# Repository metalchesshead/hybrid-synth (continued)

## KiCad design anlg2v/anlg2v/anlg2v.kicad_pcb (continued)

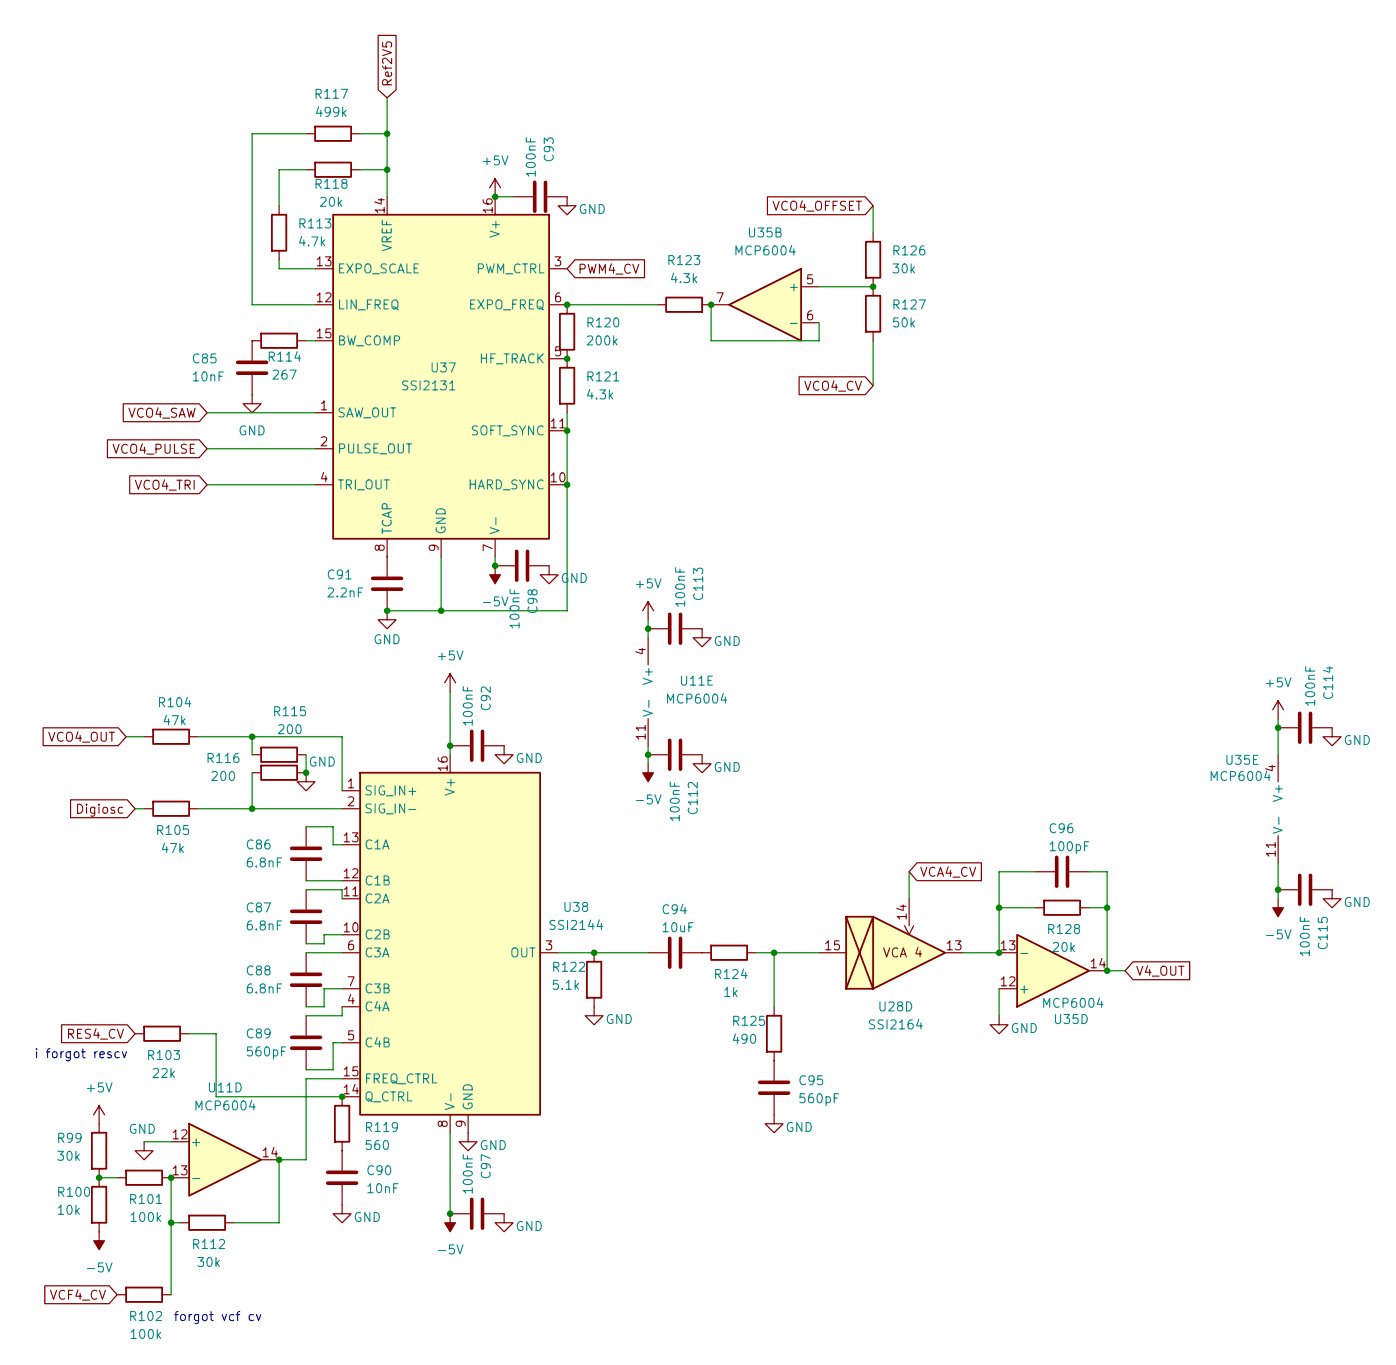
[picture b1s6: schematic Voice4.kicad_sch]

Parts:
C85, C90: 10nF; C_0402_1005Metric_Pad0.74x0.62mm_HandSolder
C86, C87, C88: 6.8nF; C_0402_1005Metric_Pad0.74x0.62mm_HandSolder
C89, C95: 560pF; C_0402_1005Metric_Pad0.74x0.62mm_HandSolder
C91: 2.2nF; C_0402_1005Metric_Pad0.74x0.62mm_HandSolder
C92, C93, C97, C98, C112, C113, C114, C115: 100nF; C_0402_1005Metric_Pad0.74x0.62mm_HandSolder
C94: 10uF; C_0402_1005Metric_Pad0.74x0.62mm_HandSolder
C96: 100pF; C_0402_1005Metric_Pad0.74x0.62mm_HandSolder
R99, R112, R126: 30k; R_0402_1005Metric
R100: 10k; R_0402_1005Metric
R101, R102: 100k; R_0402_1005Metric
R103: 22k; R_0402_1005Metric
R104, R105: 47k; R_0402_1005Metric
R113: 4.7k; R_0402_1005Metric
R114: 267; R_0402_1005Metric
R115, R116: 200; R_0402_1005Metric
R117: 499k; R_0402_1005Metric
R118, R128: 20k; R_0402_1005Metric
R119: 560; R_0402_1005Metric
R120: 200k; R_0402_1005Metric
R121, R123: 4.3k; R_0402_1005Metric
R122: 5.1k; R_0402_1005Metric
R124: 1k; R_0402_1005Metric
R125: 490; R_0402_1005Metric
R127: 50k; R_0402_1005Metric
U11, U35: MCP6004; SOIC-14_3.9x8.7mm_P1.27mm
U28: SSI2164; SOP-16_3.9x9.9mm_P1.27mm
U37: SSI2131; STC_SOP-16_3.9x9.9mm_P1.27mm
U38: SSI2144; SSOP-16_3.9x4.9mm_P0.635mm

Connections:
+5V: C92.2, C93.2, C113.2, C114.2, R99.1, U11.4 (V+), U35.4 (V+), U37.16 (V+), U38.16 (V+); also elsewhere on the board
-5V: C97.2, C98.2, C112.2, C115.2, R100.2, U11.11 (V-), U35.11 (V-), U37.7 (V-), U38.8 (V-); also elsewhere on the board
GND: C85.2, C90.2, C91.2, C92.1, C93.1, C95.2, C97.1, C98.1, C112.1, C113.1, C114.1, C115.1, R115.1, R116.1, R121.2, R122.2, U11.12 (+), U35.12 (+), U37.9 (GND), U37.10 (HARD_SYNC), U37.11 (SOFT_SYNC), U38.9 (GND); also elsewhere on the board
unnamed: C85.1, R114.2
unnamed: C90.1, R119.2
unnamed: C94.2, R124.2
unnamed: C95.1, R125.2
unnamed: R99.2, R100.1, R101.2
unnamed: R113.1, R118.2
unnamed: R124.1, R125.1, U28.15
unnamed: R101.1, R102.1, R112.2, U11.13 (-)
unnamed: R126.2, R127.1, U35.5 (+)
unnamed: R123.2, U35.6 (-), U35.7
unnamed: C96.1, R128.2, U28.13, U35.13 (-)
unnamed: R114.1, U37.15 (BW_COMP)
unnamed: R120.1, R123.1, U37.6 (EXPO_FREQ)
unnamed: R113.2, U37.13 (EXPO_SCALE)
unnamed: R120.2, R121.1, U37.5 (HF_TRACK)
unnamed: R117.2, U37.12 (LIN_FREQ)
unnamed: C91.1, U37.8 (TCAP)
unnamed: C86.1, U38.13 (C1A)
unnamed: C86.2, U38.12 (C1B)
unnamed: C87.1, U38.11 (C2A)
unnamed: C87.2, U38.10 (C2B)
unnamed: C88.1, U38.6 (C3A)
unnamed: C88.2, U38.7 (C3B)
unnamed: C89.1, U38.4 (C4A)
unnamed: C89.2, U38.5 (C4B)
unnamed: R112.1, U11.14, U38.15 (FREQ_CTRL)
unnamed: C94.1, R122.1, U38.3 (OUT)
unnamed: R103.1, R119.1, U38.14 (Q_CTRL)
unnamed: R104.1, R115.2, U38.1 (SIG_IN+)
unnamed: R105.1, R116.2, U38.2 (SIG_IN-)
PWM4_CV: U37.3 (PWM_CTRL); also elsewhere on the board
RES4_CV: R103.2; also elsewhere on the board
Ref2V5: R117.1, R118.1, U37.14 (VREF); also elsewhere on the board
V4_OUT: C96.2, R128.1, U35.14; also elsewhere on the board
VCA4_CV: U28.14; also elsewhere on the board
VCF4_CV: R102.2; also elsewhere on the board
VCO4_CV: R127.2; also elsewhere on the board
VCO4_OFFSET: R126.1; also elsewhere on the board
VCO4_OUT: R104.2; also elsewhere on the board
VCO4_PULSE: U37.2 (PULSE_OUT); also elsewhere on the board
VCO4_SAW: U37.1 (SAW_OUT); also elsewhere on the board
VCO4_TRI: U37.4 (TRI_OUT); also elsewhere on the board

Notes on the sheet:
forgot vcf cv
i forgot rescv

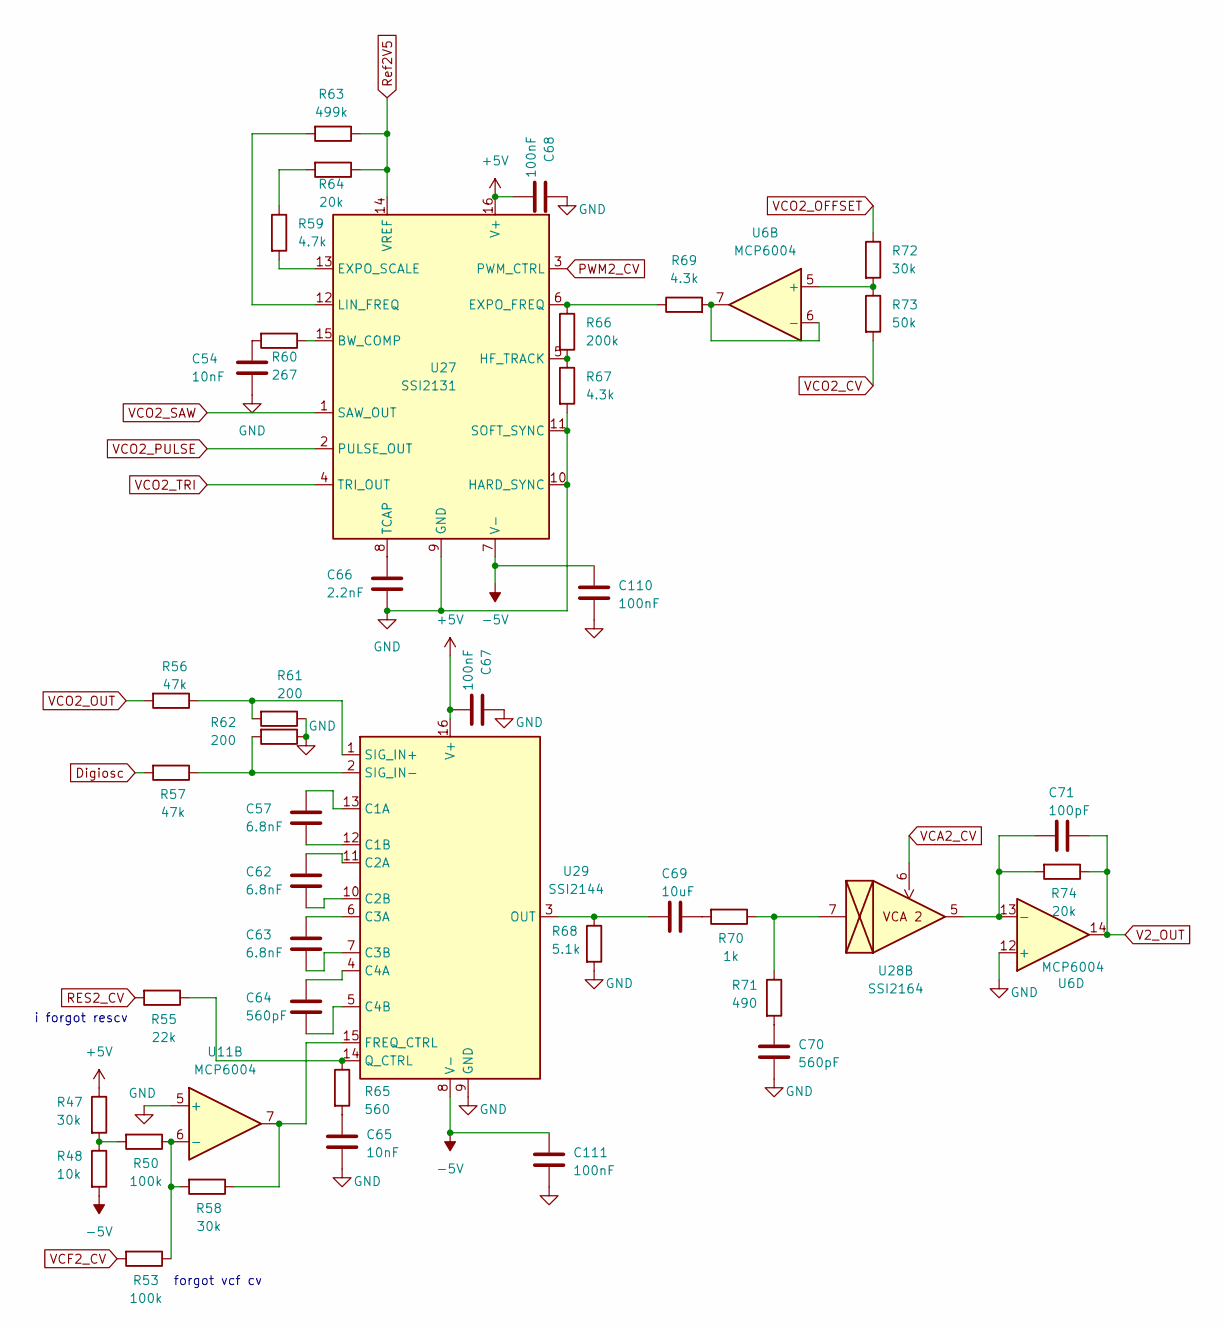
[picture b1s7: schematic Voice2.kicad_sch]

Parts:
C54, C65: 10nF; C_0402_1005Metric_Pad0.74x0.62mm_HandSolder
C57, C62, C63: 6.8nF; C_0402_1005Metric_Pad0.74x0.62mm_HandSolder
C64, C70: 560pF; C_0402_1005Metric_Pad0.74x0.62mm_HandSolder
C66: 2.2nF; C_0402_1005Metric_Pad0.74x0.62mm_HandSolder
C67, C68, C110, C111: 100nF; C_0402_1005Metric_Pad0.74x0.62mm_HandSolder
C69: 10uF; C_0402_1005Metric_Pad0.74x0.62mm_HandSolder
C71: 100pF; C_0402_1005Metric_Pad0.74x0.62mm_HandSolder
R47, R58, R72: 30k; R_0402_1005Metric
R48: 10k; R_0402_1005Metric
R50, R53: 100k; R_0402_1005Metric
R55: 22k; R_0402_1005Metric
R56, R57: 47k; R_0402_1005Metric
R59: 4.7k; R_0402_1005Metric
R60: 267; R_0402_1005Metric
R61, R62: 200; R_0402_1005Metric
R63: 499k; R_0402_1005Metric
R64, R74: 20k; R_0402_1005Metric
R65: 560; R_0402_1005Metric
R66: 200k; R_0402_1005Metric
R67, R69: 4.3k; R_0402_1005Metric
R68: 5.1k; R_0402_1005Metric
R70: 1k; R_0402_1005Metric
R71: 490; R_0402_1005Metric
R73: 50k; R_0402_1005Metric
U6, U11: MCP6004; SOIC-14_3.9x8.7mm_P1.27mm
U27: SSI2131; STC_SOP-16_3.9x9.9mm_P1.27mm
U28: SSI2164; SOP-16_3.9x9.9mm_P1.27mm
U29: SSI2144; SSOP-16_3.9x4.9mm_P0.635mm

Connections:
+5V: C67.2, C68.2, R47.1, U27.16 (V+), U29.16 (V+); also elsewhere on the board
-5V: C110.1, C111.1, R48.2, U27.7 (V-), U29.8 (V-); also elsewhere on the board
GND: C54.2, C65.2, C66.2, C67.1, C68.1, C70.2, C110.2, C111.2, R61.1, R62.1, R67.2, R68.2, U6.12 (+), U11.5 (+), U27.9 (GND), U27.10 (HARD_SYNC), U27.11 (SOFT_SYNC), U29.9 (GND); also elsewhere on the board
unnamed: C54.1, R60.2
unnamed: C65.1, R65.2
unnamed: C69.2, R70.2
unnamed: C70.1, R71.2
unnamed: R47.2, R48.1, R50.2
unnamed: R59.1, R64.2
unnamed: R70.1, R71.1, U28.7
unnamed: R72.2, R73.1, U6.5 (+)
unnamed: R69.2, U6.6 (-), U6.7
unnamed: C71.1, R74.2, U6.13 (-), U28.5
unnamed: R50.1, R53.1, R58.2, U11.6 (-)
unnamed: R60.1, U27.15 (BW_COMP)
unnamed: R66.1, R69.1, U27.6 (EXPO_FREQ)
unnamed: R59.2, U27.13 (EXPO_SCALE)
unnamed: R66.2, R67.1, U27.5 (HF_TRACK)
unnamed: R63.2, U27.12 (LIN_FREQ)
unnamed: C66.1, U27.8 (TCAP)
unnamed: C57.1, U29.13 (C1A)
unnamed: C57.2, U29.12 (C1B)
unnamed: C62.1, U29.11 (C2A)
unnamed: C62.2, U29.10 (C2B)
unnamed: C63.1, U29.6 (C3A)
unnamed: C63.2, U29.7 (C3B)
unnamed: C64.1, U29.4 (C4A)
unnamed: C64.2, U29.5 (C4B)
unnamed: R58.1, U11.7, U29.15 (FREQ_CTRL)
unnamed: C69.1, R68.1, U29.3 (OUT)
unnamed: R55.1, R65.1, U29.14 (Q_CTRL)
unnamed: R56.1, R61.2, U29.1 (SIG_IN+)
unnamed: R57.1, R62.2, U29.2 (SIG_IN-)
PWM2_CV: U27.3 (PWM_CTRL); also elsewhere on the board
RES2_CV: R55.2; also elsewhere on the board
Ref2V5: R63.1, R64.1, U27.14 (VREF); also elsewhere on the board
V2_OUT: C71.2, R74.1, U6.14; also elsewhere on the board
VCA2_CV: U28.6; also elsewhere on the board
VCF2_CV: R53.2; also elsewhere on the board
VCO2_CV: R73.2; also elsewhere on the board
VCO2_OFFSET: R72.1; also elsewhere on the board
VCO2_OUT: R56.2; also elsewhere on the board
VCO2_PULSE: U27.2 (PULSE_OUT); also elsewhere on the board
VCO2_SAW: U27.1 (SAW_OUT); also elsewhere on the board
VCO2_TRI: U27.4 (TRI_OUT); also elsewhere on the board

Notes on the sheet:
i forgot rescv
forgot vcf cv

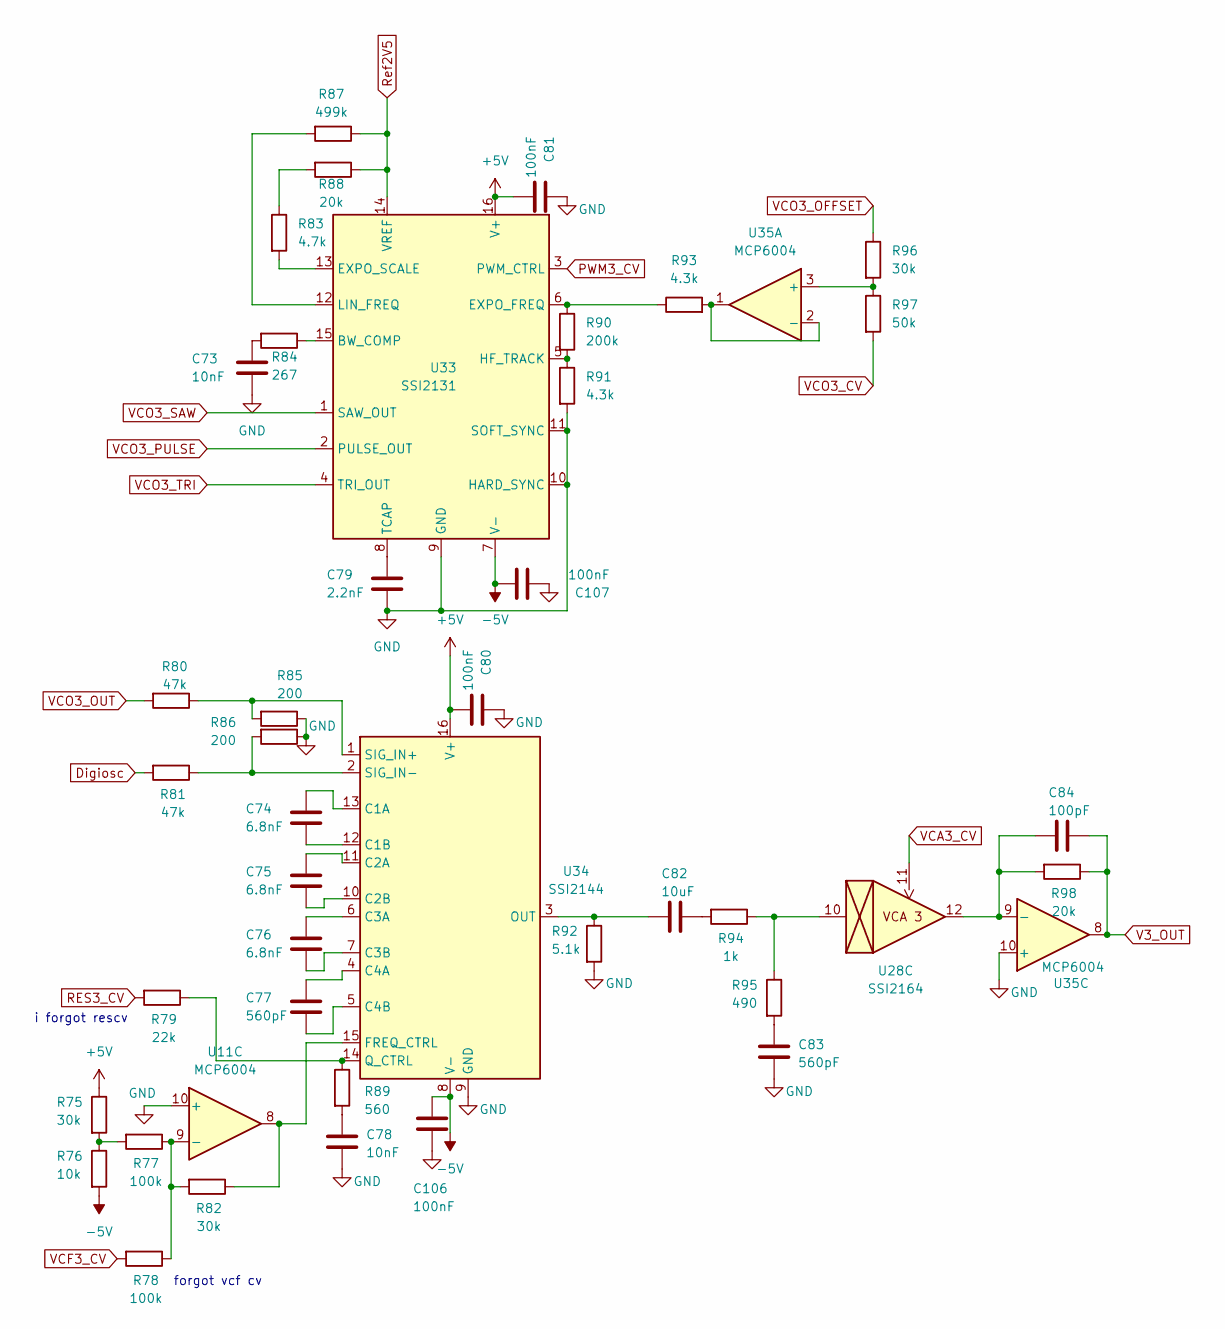
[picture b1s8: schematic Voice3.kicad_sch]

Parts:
C73, C78: 10nF; C_0402_1005Metric_Pad0.74x0.62mm_HandSolder
C74, C75, C76: 6.8nF; C_0402_1005Metric_Pad0.74x0.62mm_HandSolder
C77, C83: 560pF; C_0402_1005Metric_Pad0.74x0.62mm_HandSolder
C79: 2.2nF; C_0402_1005Metric_Pad0.74x0.62mm_HandSolder
C80, C81, C106, C107: 100nF; C_0402_1005Metric_Pad0.74x0.62mm_HandSolder
C82: 10uF; C_0402_1005Metric_Pad0.74x0.62mm_HandSolder
C84: 100pF; C_0402_1005Metric_Pad0.74x0.62mm_HandSolder
R75, R82, R96: 30k; R_0402_1005Metric
R76: 10k; R_0402_1005Metric
R77, R78: 100k; R_0402_1005Metric
R79: 22k; R_0402_1005Metric
R80, R81: 47k; R_0402_1005Metric
R83: 4.7k; R_0402_1005Metric
R84: 267; R_0402_1005Metric
R85, R86: 200; R_0402_1005Metric
R87: 499k; R_0402_1005Metric
R88, R98: 20k; R_0402_1005Metric
R89: 560; R_0402_1005Metric
R90: 200k; R_0402_1005Metric
R91, R93: 4.3k; R_0402_1005Metric
R92: 5.1k; R_0402_1005Metric
R94: 1k; R_0402_1005Metric
R95: 490; R_0402_1005Metric
R97: 50k; R_0402_1005Metric
U11, U35: MCP6004; SOIC-14_3.9x8.7mm_P1.27mm
U28: SSI2164; SOP-16_3.9x9.9mm_P1.27mm
U33: SSI2131; STC_SOP-16_3.9x9.9mm_P1.27mm
U34: SSI2144; SSOP-16_3.9x4.9mm_P0.635mm

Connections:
+5V: C80.2, C81.2, R75.1, U33.16 (V+), U34.16 (V+); also elsewhere on the board
-5V: C106.1, C107.1, R76.2, U33.7 (V-), U34.8 (V-); also elsewhere on the board
GND: C73.2, C78.2, C79.2, C80.1, C81.1, C83.2, C106.2, C107.2, R85.1, R86.1, R91.2, R92.2, U11.10 (+), U33.9 (GND), U33.10 (HARD_SYNC), U33.11 (SOFT_SYNC), U34.9 (GND), U35.10 (+); also elsewhere on the board
unnamed: C73.1, R84.2
unnamed: C78.1, R89.2
unnamed: C82.2, R94.2
unnamed: C83.1, R95.2
unnamed: R75.2, R76.1, R77.2
unnamed: R83.1, R88.2
unnamed: R94.1, R95.1, U28.10
unnamed: R77.1, R78.1, R82.2, U11.9 (-)
unnamed: R84.1, U33.15 (BW_COMP)
unnamed: R90.1, R93.1, U33.6 (EXPO_FREQ)
unnamed: R83.2, U33.13 (EXPO_SCALE)
unnamed: R90.2, R91.1, U33.5 (HF_TRACK)
unnamed: R87.2, U33.12 (LIN_FREQ)
unnamed: C79.1, U33.8 (TCAP)
unnamed: C74.1, U34.13 (C1A)
unnamed: C74.2, U34.12 (C1B)
unnamed: C75.1, U34.11 (C2A)
unnamed: C75.2, U34.10 (C2B)
unnamed: C76.1, U34.6 (C3A)
unnamed: C76.2, U34.7 (C3B)
unnamed: C77.1, U34.4 (C4A)
unnamed: C77.2, U34.5 (C4B)
unnamed: R82.1, U11.8, U34.15 (FREQ_CTRL)
unnamed: C82.1, R92.1, U34.3 (OUT)
unnamed: R79.1, R89.1, U34.14 (Q_CTRL)
unnamed: R80.1, R85.2, U34.1 (SIG_IN+)
unnamed: R81.1, R86.2, U34.2 (SIG_IN-)
unnamed: R96.2, R97.1, U35.3 (+)
unnamed: R93.2, U35.1, U35.2 (-)
unnamed: C84.1, R98.2, U28.12, U35.9 (-)
PWM3_CV: U33.3 (PWM_CTRL); also elsewhere on the board
RES3_CV: R79.2; also elsewhere on the board
Ref2V5: R87.1, R88.1, U33.14 (VREF); also elsewhere on the board
V3_OUT: C84.2, R98.1, U35.8; also elsewhere on the board
VCA3_CV: U28.11; also elsewhere on the board
VCF3_CV: R78.2; also elsewhere on the board
VCO3_CV: R97.2; also elsewhere on the board
VCO3_OFFSET: R96.1; also elsewhere on the board
VCO3_OUT: R80.2; also elsewhere on the board
VCO3_PULSE: U33.2 (PULSE_OUT); also elsewhere on the board
VCO3_SAW: U33.1 (SAW_OUT); also elsewhere on the board
VCO3_TRI: U33.4 (TRI_OUT); also elsewhere on the board

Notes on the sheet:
forgot vcf cv
i forgot rescv

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
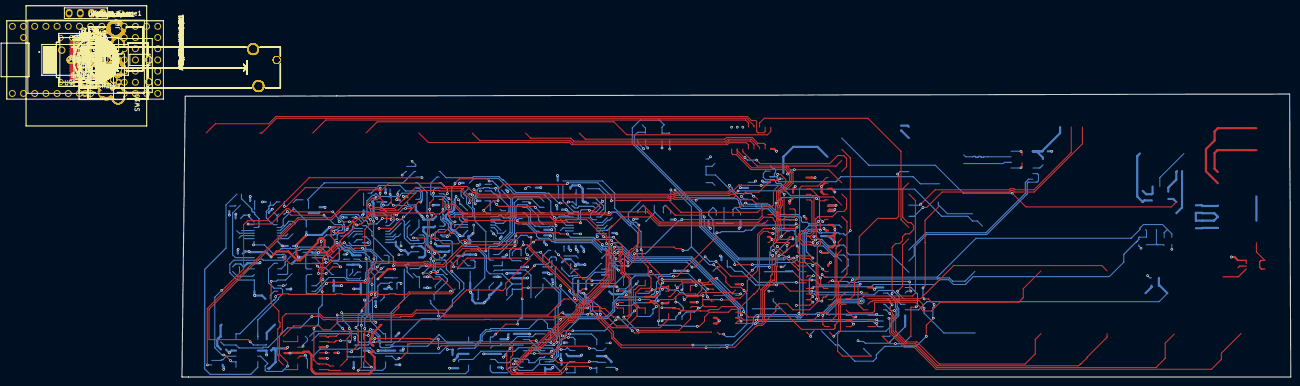
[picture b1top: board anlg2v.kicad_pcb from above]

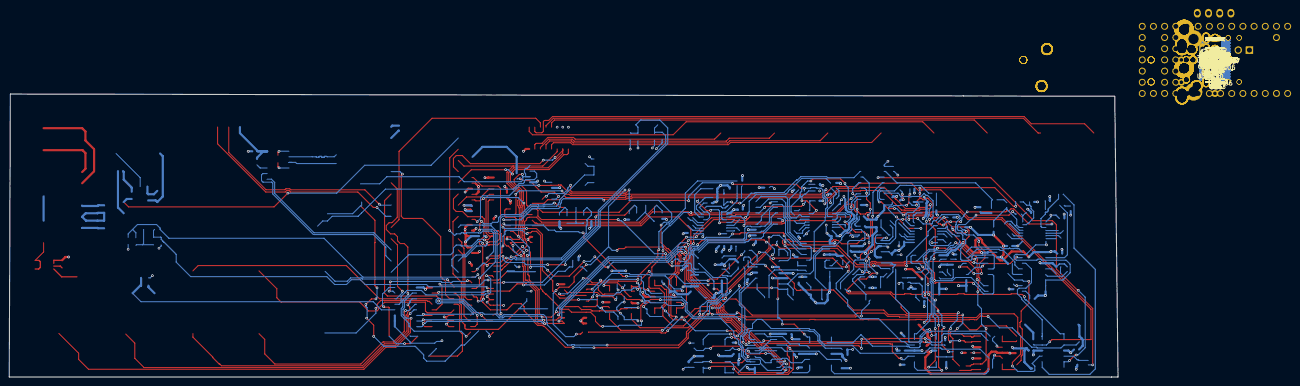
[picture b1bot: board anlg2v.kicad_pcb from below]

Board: 4 copper layers, 251.8 x 64.2 mm, 321 parts (254 on the bottom side), 272 nets.

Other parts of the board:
C10, C11: 1000pF; CP_Radial_D10.0mm_P5.00mm

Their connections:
GND: C11.2; also elsewhere on the board
unnamed 22: C10.2; also elsewhere on the board

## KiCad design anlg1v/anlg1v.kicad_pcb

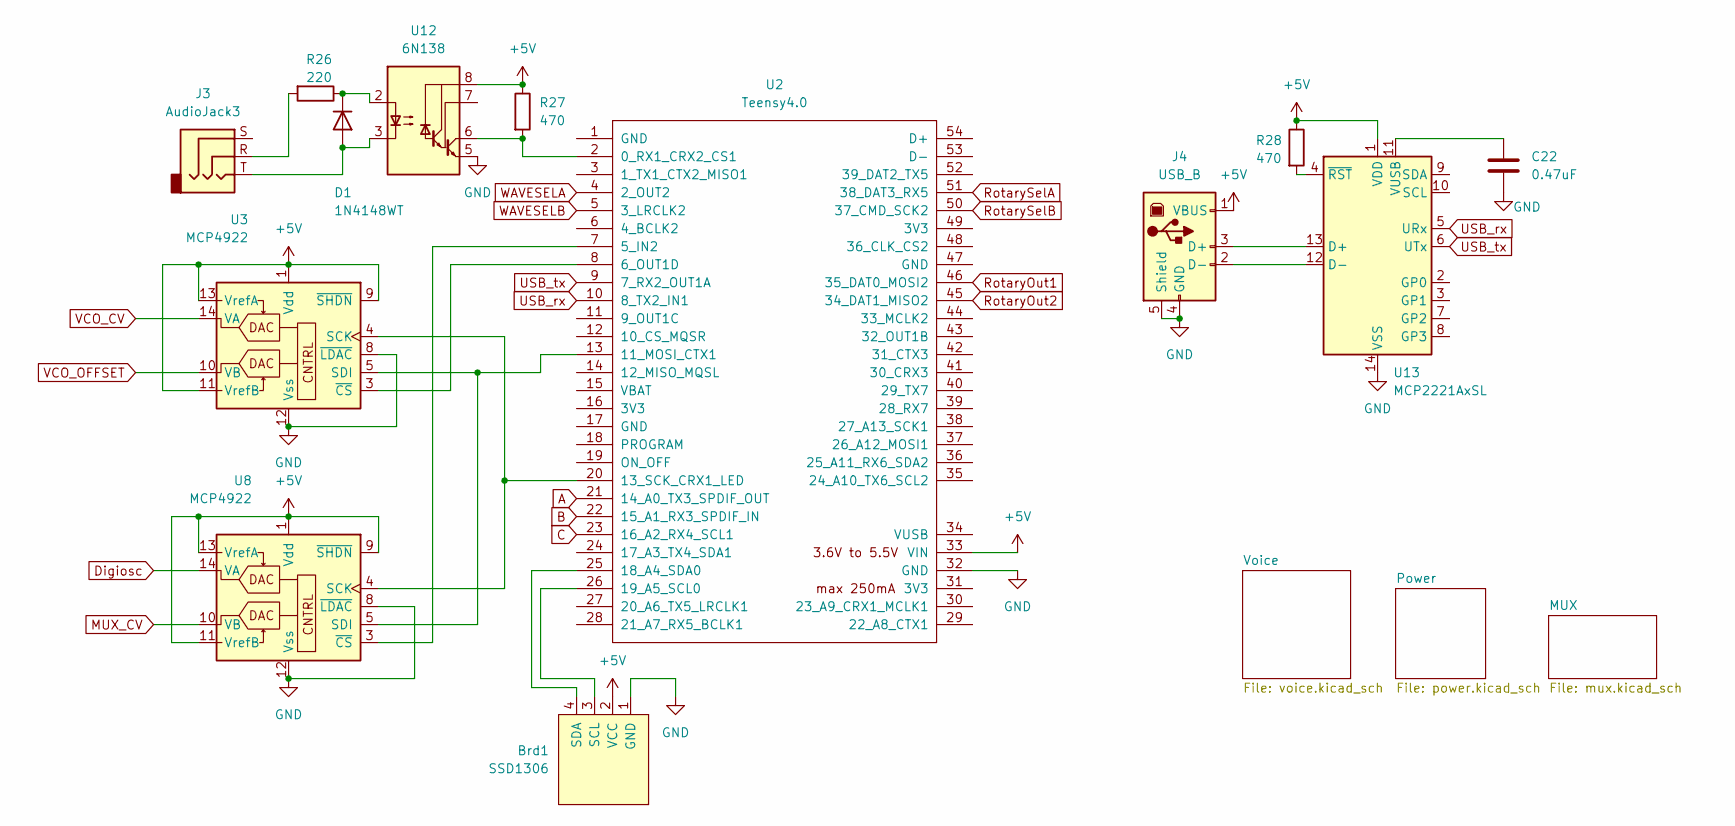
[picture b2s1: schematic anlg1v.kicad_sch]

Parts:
Brd1: SSD1306; 128x64OLED
C22: 0.47uF; C_0603_1608Metric_Pad1.08x0.95mm_HandSolder
D1: 1N4148WT; D_SOD-523
J3: AudioJack3; PJ-307
J4: USB_B; USB_B_Lumberg_2411_02_Horizontal
R26: 220; R_0603_1608Metric
R27, R28: 470; R_0603_1608Metric
U2: Teensy4.0; Teensy40
U3, U8: MCP4922; SOIC-14_3.9x8.7mm_P1.27mm
U12: 6N138; DIP-8_W7.62mm_Socket
U13: MCP2221AxSL; SOIC-14_3.9x8.7mm_P1.27mm

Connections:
+5V: Brd1.2 (VCC), J4.1 (VBUS), R27.1, R28.1, U2.33 (VIN), U3.1 (Vdd), U3.9 (~SHDN), U3.11 (VrefB), U3.13 (VrefA), U8.1 (Vdd), U8.9 (~SHDN), U8.11 (VrefB), U8.13 (VrefA), U12.8 (VCC), U13.1 (VDD); also elsewhere on the board
A: U2.21 (14_A0_TX3_SPDIF_OUT); also elsewhere on the board
B: U2.22 (15_A1_RX3_SPDIF_IN); also elsewhere on the board
C: U2.23 (16_A2_RX4_SCL1); also elsewhere on the board
Digiosc: U8.14 (VA); also elsewhere on the board
GND: Brd1.1 (GND), C22.2, J4.4 (GND), J4.5 (Shield), U2.32 (GND), U3.8 (~LDAC), U3.12 (Vss), U8.8 (~LDAC), U8.12 (Vss), U12.5 (GND), U13.14 (VSS); also elsewhere on the board
MUX1: U2.24 (17_A3_TX4_SDA1); also elsewhere on the board
MUX2: U2.27 (20_A6_TX5_LRCLK1); also elsewhere on the board
MUX3: U2.28 (21_A7_RX5_BCLK1); also elsewhere on the board
MUX_CV: U8.10 (VB); also elsewhere on the board
unnamed: Brd1.3 (SCL), U2.26 (19_A5_SCL0)
unnamed: Brd1.4 (SDA), U2.25 (18_A4_SDA0)
unnamed: D1.2 (A), J3.T, U12.3 (C2)
unnamed: D1.1 (K), R26.1, U12.2 (C1)
unnamed: J3.R, R26.2
unnamed: J4.3 (D+), U13.13 (D+)
unnamed: J4.2 (D-), U13.12 (D-)
unnamed: U2.7 (5_IN2), U8.3 (~CS)
unnamed: U2.8 (6_OUT1D), U3.3 (~CS)
unnamed: U2.13 (11_MOSI_CTX1), U3.5 (SDI), U8.5 (SDI)
unnamed: U2.20 (13_SCK_CRX1_LED), U3.4 (SCK), U8.4 (SCK)
unnamed: R27.2, U2.2 (0_RX1_CRX2_CS1), U12.6 (VO2)
unnamed: C22.1, U13.11 (VUSB)
unnamed: R28.2, U13.4 (~RST)
RotaryOut1: U2.30 (23_A9_CRX1_MCLK1); also elsewhere on the board
RotaryOut2: U2.29 (22_A8_CTX1); also elsewhere on the board
RotarySelA: U2.11 (9_OUT1C); also elsewhere on the board
RotarySelB: U2.12 (10_CS_MQSR); also elsewhere on the board
USB_rx: U2.10 (8_TX2_IN1), U13.5 (URx)
USB_tx: U2.9 (7_RX2_OUT1A), U13.6 (UTx)
VCO_CV: U3.14 (VA); also elsewhere on the board
VCO_OFFSET: U3.10 (VB); also elsewhere on the board
WAVESELA: U2.4 (2_OUT2); also elsewhere on the board
WAVESELB: U2.5 (3_LRCLK2); also elsewhere on the board

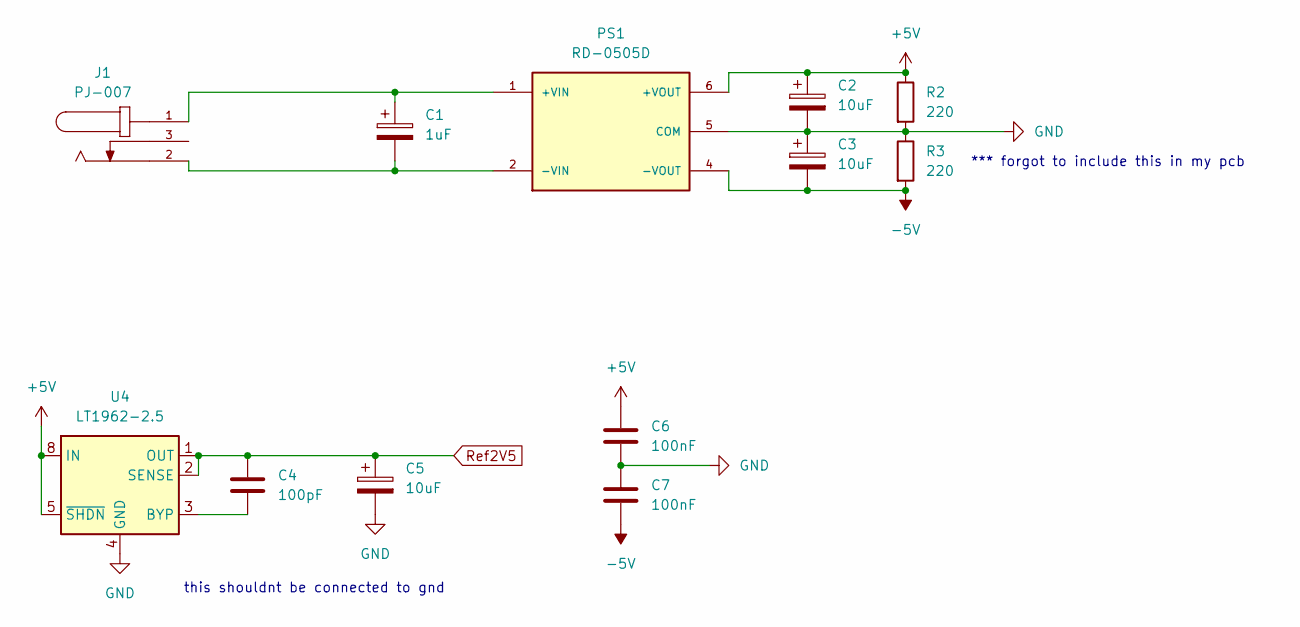
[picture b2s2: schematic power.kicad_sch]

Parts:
C1: 1uF; CP_Radial_D10.0mm_P5.00mm
C2, C3, C5: 10uF; CP_Radial_D10.0mm_P5.00mm
C4: 100pF; C_0603_1608Metric_Pad1.08x0.95mm_HandSolder
C6, C7: 100nF; C_0603_1608Metric_Pad1.08x0.95mm_HandSolder
J1: PJ-007; SAMESKY_PJ-007; PARTREV 1.07
PS1: RD-0505D; CONV_RD-0505D; PARTREV 1
R2, R3: 220; R_0603_1608Metric
U4: LT1962-2.5; MSOP-8_3x3mm_P0.65mm

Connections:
+5V: C2.1, C6.1, PS1.6 (+VOUT), R2.1, U4.5 (~SHDN), U4.8 (IN); also elsewhere on the board
-5V: C3.2, C7.2, PS1.4 (-VOUT), R3.2; also elsewhere on the board
GND: C2.2, C3.1, C5.2, C6.2, C7.1, PS1.5 (COM), R2.2, R3.1, U4.4 (GND); also elsewhere on the board
unnamed: C1.1, J1.1, PS1.1 (+VIN)
unnamed: C1.2, J1.2, PS1.2 (-VIN)
unnamed: C4.2, U4.3 (BYP)
Ref2V5: C4.1, C5.1, U4.1 (OUT), U4.2 (SENSE); also elsewhere on the board

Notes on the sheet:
*** forgot to include this in my pcb
this shouldnt be connected to gnd

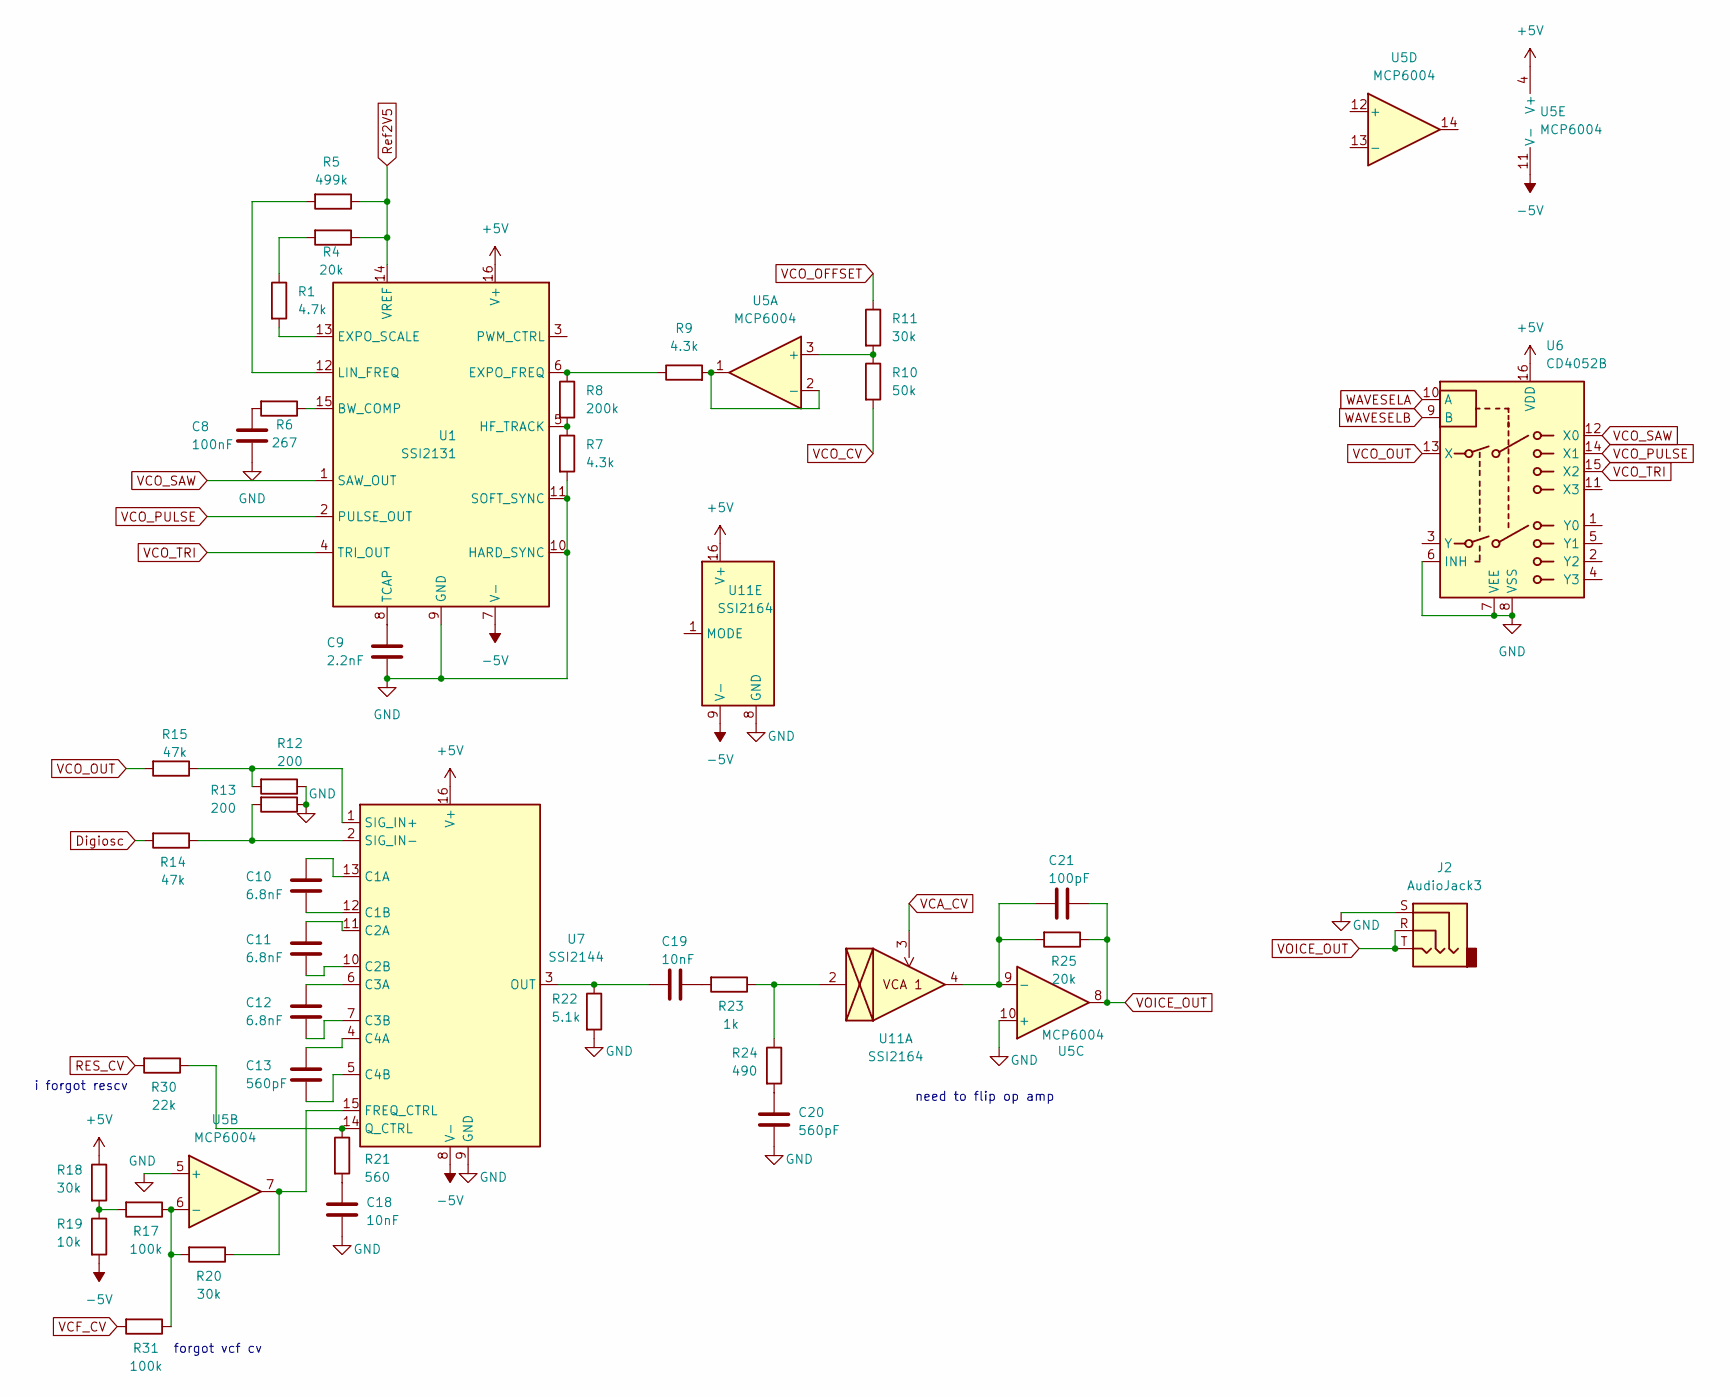
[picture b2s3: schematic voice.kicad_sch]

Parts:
C8: 100nF; C_0603_1608Metric_Pad1.08x0.95mm_HandSolder
C9: 2.2nF; C_0603_1608Metric_Pad1.08x0.95mm_HandSolder
C10, C11, C12: 6.8nF; C_0603_1608Metric_Pad1.08x0.95mm_HandSolder
C13, C20: 560pF; C_0603_1608Metric_Pad1.08x0.95mm_HandSolder
C18, C19: 10nF; C_0603_1608Metric_Pad1.08x0.95mm_HandSolder
C21: 100pF; C_0603_1608Metric_Pad1.08x0.95mm_HandSolder
J2: AudioJack3; PJ-307
R1: 4.7k; R_0603_1608Metric
R4, R25: 20k; R_0603_1608Metric
R5: 499k; R_0603_1608Metric
R6: 267; R_0603_1608Metric
R7, R9: 4.3k; R_0603_1608Metric
R8: 200k; R_0603_1608Metric
R10: 50k; R_0603_1608Metric
R11, R18, R20: 30k; R_0603_1608Metric
R12, R13: 200; R_0603_1608Metric
R14, R15: 47k; R_0603_1608Metric
R17, R31: 100k; R_0603_1608Metric
R19: 10k; R_0603_1608Metric
R21: 560; R_0603_1608Metric
R22: 5.1k; R_0603_1608Metric
R23: 1k; R_0603_1608Metric
R24: 490; R_0603_1608Metric
R30: 22k; R_0603_1608Metric
U1: SSI2131; STC_SOP-16_3.9x9.9mm_P1.27mm
U5: MCP6004; SOIC-14_3.9x8.7mm_P1.27mm
U6: CD4052B; SOIC-16_3.9x9.9mm_P1.27mm
U7: SSI2144; SSOP-16_3.9x4.9mm_P0.635mm
U11: SSI2164; STC_SOP-16_3.9x9.9mm_P1.27mm

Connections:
+5V: R18.1, U1.16 (V+), U5.4 (V+), U6.16 (VDD), U7.16 (V+), U11.16 (V+); also elsewhere on the board
-5V: R19.2, U1.7 (V-), U5.11 (V-), U7.8 (V-), U11.9 (V-); also elsewhere on the board
Digiosc: R14.2; also elsewhere on the board
GND: C8.2, C9.2, C18.2, C20.2, J2.S, R7.2, R12.1, R13.1, R22.2, U1.9 (GND), U1.10 (HARD_SYNC), U1.11 (SOFT_SYNC), U5.5 (+), U5.10 (+), U6.6 (INH), U6.7 (VEE), U6.8 (VSS), U7.9 (GND), U11.8 (GND); also elsewhere on the board
unnamed: C8.1, R6.2
unnamed: C18.1, R21.2
unnamed: C19.2, R23.2
unnamed: C20.1, R24.2
unnamed: R1.1, R4.2
unnamed: R17.2, R18.2, R19.1
unnamed: R23.1, R24.1, U11.2
unnamed: R6.1, U1.15 (BW_COMP)
unnamed: R8.1, R9.1, U1.6 (EXPO_FREQ)
unnamed: R1.2, U1.13 (EXPO_SCALE)
unnamed: R7.1, R8.2, U1.5 (HF_TRACK)
unnamed: R5.2, U1.12 (LIN_FREQ)
unnamed: C9.1, U1.8 (TCAP)
unnamed: R10.1, R11.2, U5.3 (+)
unnamed: R9.2, U5.1, U5.2 (-)
unnamed: R17.1, R20.2, R31.1, U5.6 (-)
unnamed: C21.1, R25.2, U5.9 (-), U11.4
unnamed: C10.1, U7.13 (C1A)
unnamed: C10.2, U7.12 (C1B)
unnamed: C11.1, U7.11 (C2A)
unnamed: C11.2, U7.10 (C2B)
unnamed: C12.1, U7.6 (C3A)
unnamed: C12.2, U7.7 (C3B)
unnamed: C13.1, U7.4 (C4A)
unnamed: C13.2, U7.5 (C4B)
unnamed: R20.1, U5.7, U7.15 (FREQ_CTRL)
unnamed: C19.1, R22.1, U7.3 (OUT)
unnamed: R21.1, R30.1, U7.14 (Q_CTRL)
unnamed: R12.2, R15.1, U7.1 (SIG_IN+)
unnamed: R13.2, R14.1, U7.2 (SIG_IN-)
RES_CV: R30.2; also elsewhere on the board
Ref2V5: R4.1, R5.1, U1.14 (VREF); also elsewhere on the board
VCA_CV: U11.3; also elsewhere on the board
VCF_CV: R31.2; also elsewhere on the board
VCO_CV: R10.2; also elsewhere on the board
VCO_OFFSET: R11.1; also elsewhere on the board
VCO_OUT: R15.2, U6.13 (X)
VCO_PULSE: U1.2 (PULSE_OUT), U6.14 (X1)
VCO_SAW: U1.1 (SAW_OUT), U6.12 (X0)
VCO_TRI: U1.4 (TRI_OUT), U6.15 (X2)
VOICE_OUT: C21.2, J2.R, J2.T, R25.1, U5.8
WAVESELA: U6.10 (A); also elsewhere on the board
WAVESELB: U6.9 (B); also elsewhere on the board

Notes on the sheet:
forgot vcf cv
need to flip op amp
i forgot rescv
